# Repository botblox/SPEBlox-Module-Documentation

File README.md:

# SPEBlox-Module-Documentation
Design files associated with SPEBlox Module for Design Integration

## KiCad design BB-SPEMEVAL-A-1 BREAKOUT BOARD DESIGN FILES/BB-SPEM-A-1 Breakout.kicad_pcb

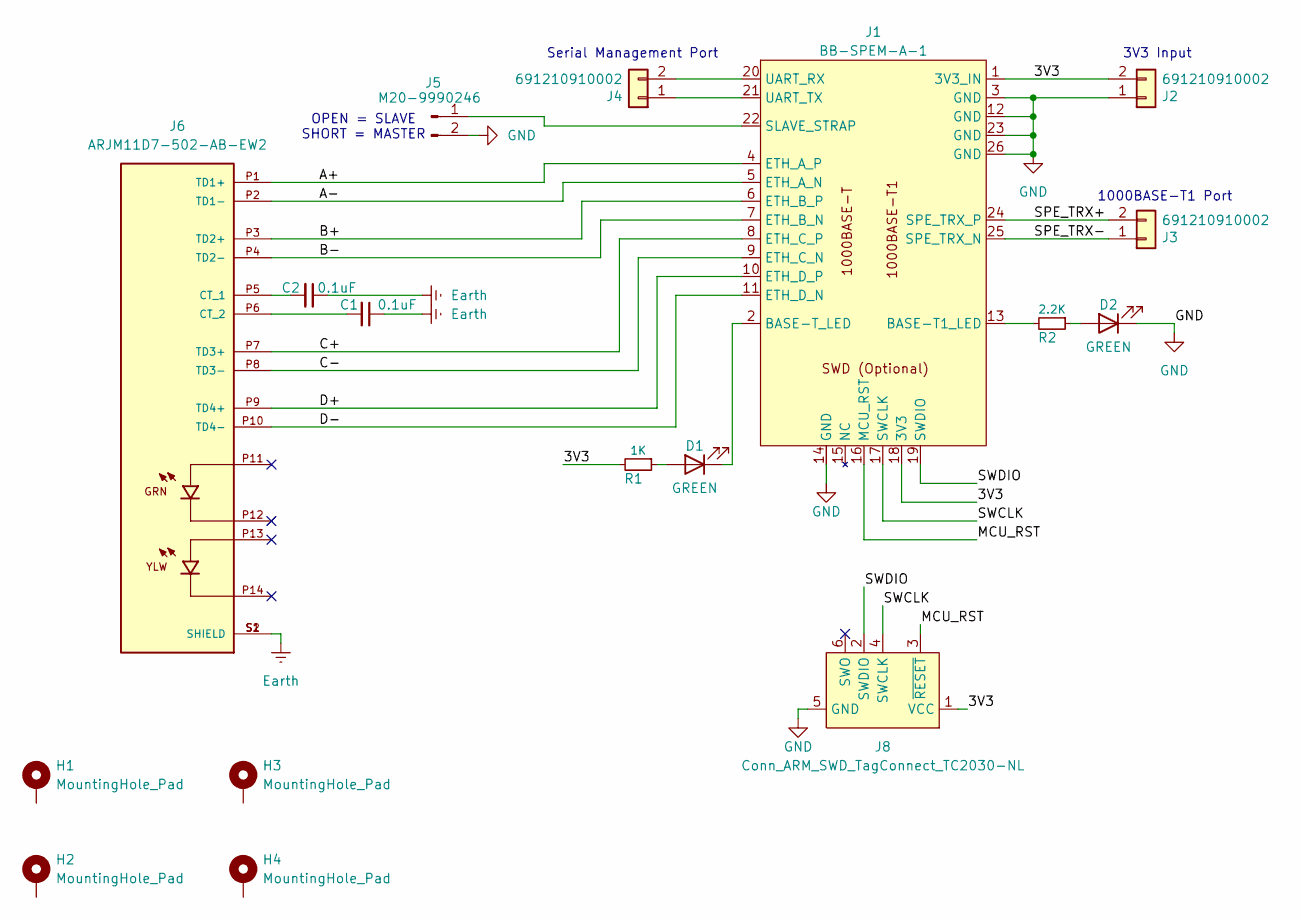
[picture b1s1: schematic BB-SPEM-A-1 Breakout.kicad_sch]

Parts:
C1, C2: 0.1uF; C_0402_Small; Voltage Rating 50V; MPN GRM155R71H104KE14J; LCSC# C85858
D1, D2: GREEN; LED_0402_1005Metric; Voltage Rating 2.1V; MPN APHHS1005CGCK
H1, H2, H3, H4: MountingHole_Pad; MountingHole_2.2mm_M2_DIN965_Pad
J1: BB-SPEM-A-1; BB-SPEM-A-1_Footprint
J2, J3, J4: 691210910002; TerminalBlock_WurthElektronik_691210910002_1x02_P2.54mm_Hor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; MPN 691210910002; LCSC# C474920
J5: Conn_01x02_Pin; PinHeader_1x02_P2.54mm_Vertical; MPN M20-9990246
J6: ARJM11D7-502-AB-EW2; ABRACON_ARJM11D7-502-AB-EW2; MPN ARJM11D7-502-AB-EW2
J8: Conn_ARM_SWD_TagConnect_TC2030-NL; Tag-Connect_TC2030-IDC-NL_2x03_P1.27mm_Vertical
R1: 1K; R_0402_1005Metric; Tolerance 1%; MPN RC0402FR-071KL; LCSC# C106235
R2: 2.2K; R_0402_1005Metric; Tolerance 1%; MPN RC0402FR-072K2L; LCSC# C114762

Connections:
/3V3: J1.1 (3V3_IN), J1.18 (3V3), J2.2, J8.1 (VCC), R1.2
/A+: J1.4 (ETH_A_P), J6.P1 (TD1+)
/A-: J1.5 (ETH_A_N), J6.P2 (TD1-)
/B+: J1.6 (ETH_B_P), J6.P3 (TD2+)
/B-: J1.7 (ETH_B_N), J6.P4 (TD2-)
/C+: J1.8 (ETH_C_P), J6.P7 (TD3+)
/C-: J1.9 (ETH_C_N), J6.P8 (TD3-)
/D+: J1.10 (ETH_D_P), J6.P9 (TD4+)
/D-: J1.11 (ETH_D_N), J6.P10 (TD4-)
/MCU_RST: J1.16 (MCU_RST), J8.3 (~RESET)
/SPE_TRX+: J1.24 (SPE_TRX_P), J3.2
/SPE_TRX-: J1.25 (SPE_TRX_N), J3.1
/SWCLK: J1.17 (SWCLK), J8.4 (SWCLK)
/SWDIO: J1.19 (SWDIO), J8.2 (SWDIO)
Earth: C1.1, C2.1, J6.S1 (SHIELD), J6.S2 (SHIELD)
GND: D2.1 (K), J1.3 (GND), J1.12 (GND), J1.14 (GND), J1.23 (GND), J1.26 (GND), J2.1, J5.2, J8.5 (GND)
unnamed: D1.2 (A), R1.1
unnamed: D1.1 (K), J1.2 (BASE-T_LED)
unnamed: D2.2 (A), R2.1
unnamed: J1.13 (BASE-T1_LED), R2.2
unnamed: J1.22 (SLAVE_STRAP), J5.1
unnamed: J1.20 (UART_RX), J4.2
unnamed: J1.21 (UART_TX), J4.1
unnamed: C2.2, J6.P5 (CT_1)
unnamed: C1.2, J6.P6 (CT_2)

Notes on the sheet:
Serial Management Port
OPEN = SLAVE SHORT = MASTER
3V3 Input
1000BASE-T1 Port

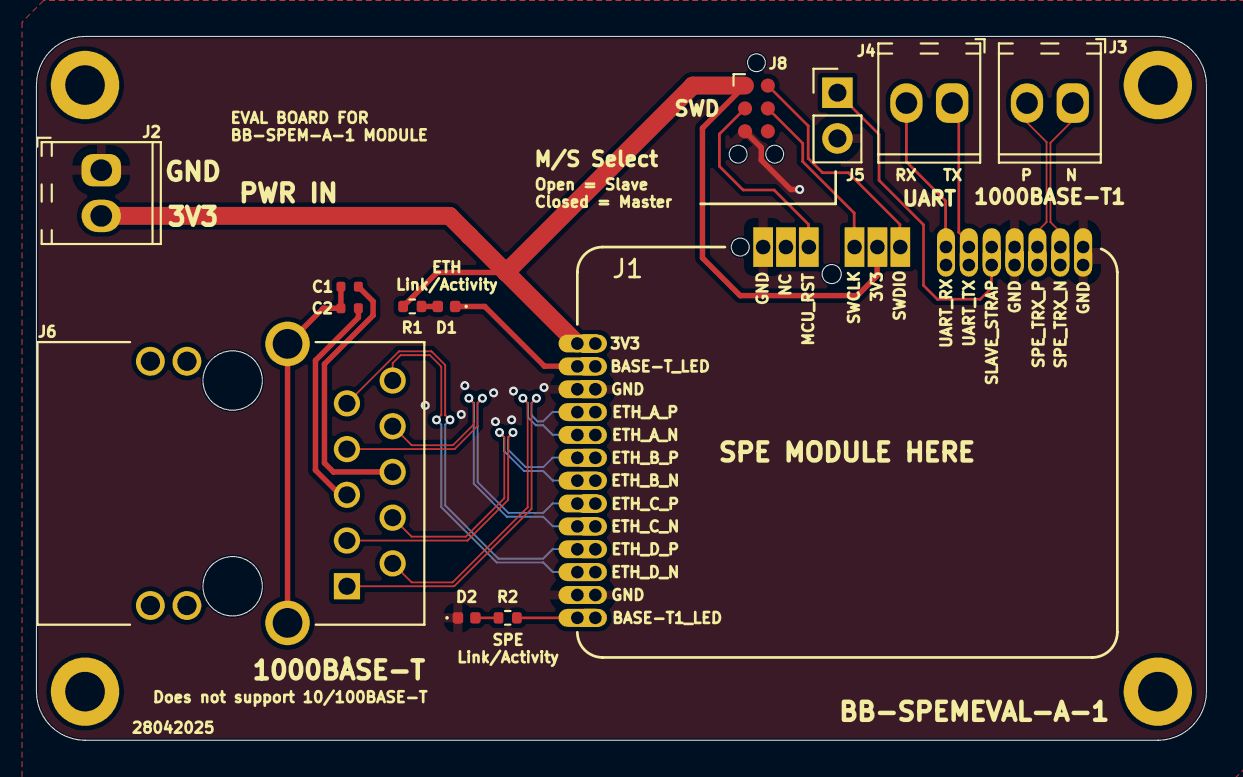
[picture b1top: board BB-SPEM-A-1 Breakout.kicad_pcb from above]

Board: 4 copper layers, 65.0 x 39.1 mm, 17 parts (0 on the bottom side), 25 nets.

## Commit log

2025-07-15 Added manufacture files
